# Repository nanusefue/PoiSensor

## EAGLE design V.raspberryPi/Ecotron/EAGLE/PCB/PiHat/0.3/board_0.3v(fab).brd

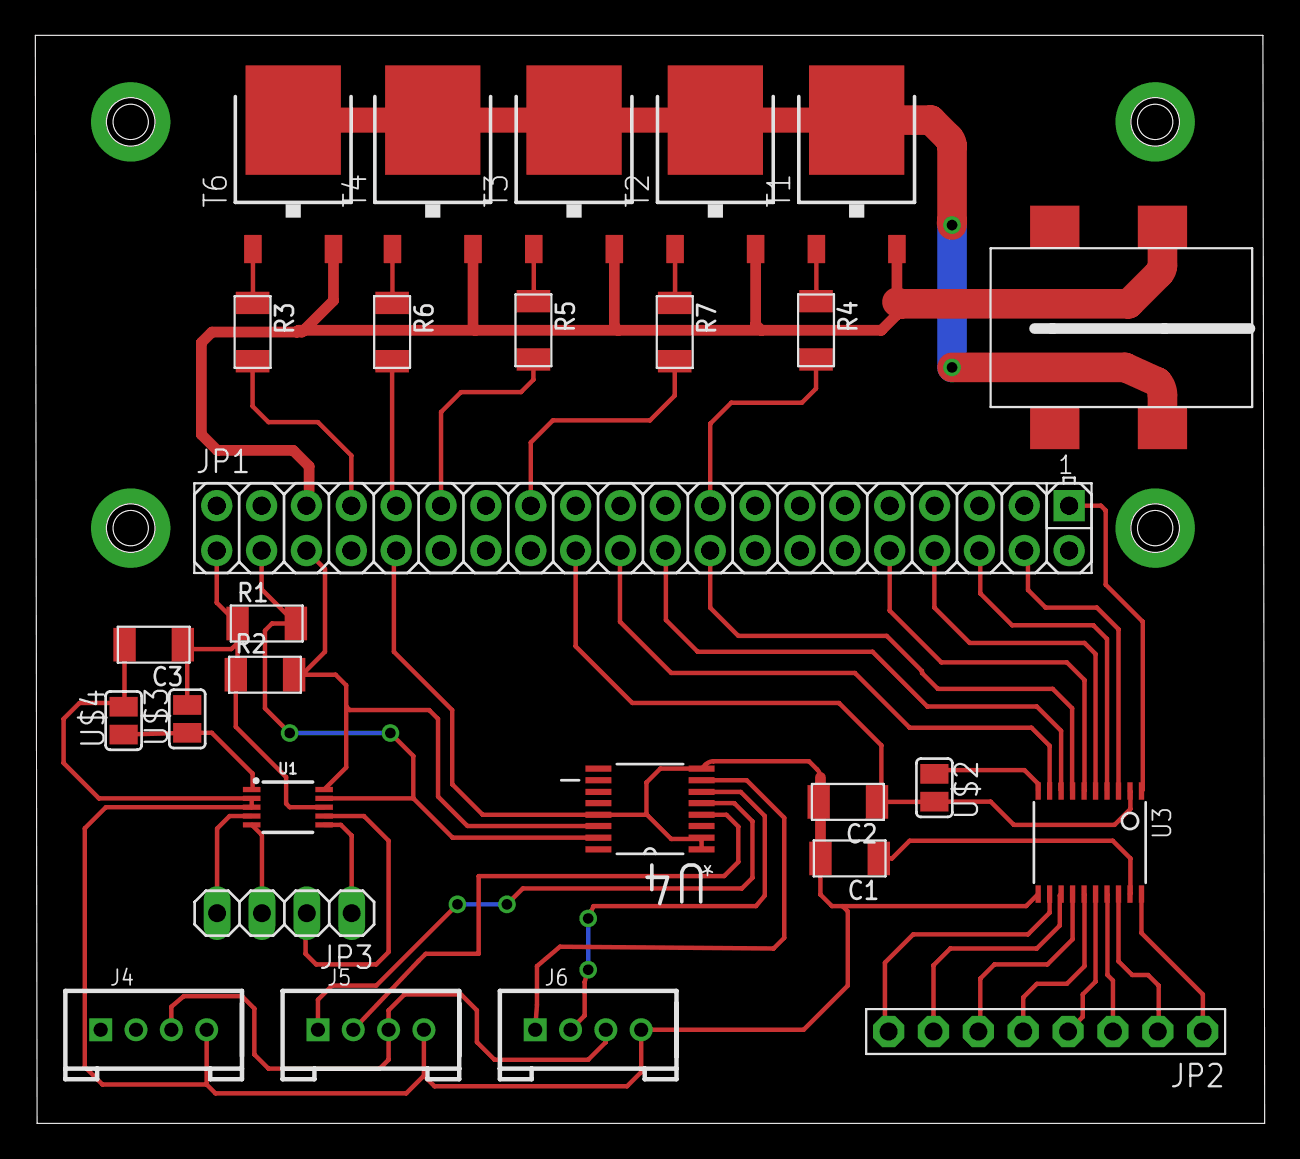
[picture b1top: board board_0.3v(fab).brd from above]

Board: 2 copper layers, 69.6 x 61.6 mm, 29 parts (0 on the bottom side), 44 nets.

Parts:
C1, C2, C3: CAP-US1206FAB; C1206FAB
J1: JACK2.1MM; JACK_2.1MM
J4, J5, J6: 4P-2.0; HW4-2.0
JP1: 2X20
JP2: 1X08-BIG
JP3: 1X04
R1, R2, R3, R4, R5, R6, R7: R1206FAB
T1, T2, T3, T4, T6: TO252
U1: ADS1015; MSOP10
U3: TSSOP20
U4: PCA9546APW,112; SOP65P640X110-16N
U$1: RPI-ZERO; RASPBERRYPI_BASTELSTUBE_V13_RASPI_BOARD_B+_FULL
U$2, U$3, U$4: SOLDER_JUMPER; SJFAB

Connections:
3,3V: C3.1, JP1.1, R1.1, R2.1, U1.8, U$3.2
3,3V_1: C2.1, JP1.17, U3.2, U$2.2
12V: J1.PIN, T1.3, T2.3, T3.3, T4.3, T6.3
A0+: JP3.4, U1.4
A0-: JP3.3, U1.5
A1+: JP3.1, U1.6
A1-: JP3.2, U1.7
ADDR_AD: U1.1, U$3.1, U$4.1
GND: C1.2, C2.2, C3.2, J1.CONTACT, J4.4, J5.4, J6.4, JP1.6, JP1.9, T1.2, T2.2, T3.2, T4.2, T6.2, U1.2, U1.3, U3.11, U4.1, U4.2, U4.8, U4.13, U$4.2
GPIO6: JP1.31, U3.6
GPIO8: JP1.24, R4.2
GPIO9: JP1.21, U3.8
GPIO10: JP1.19, U3.9
GPIO11: JP1.23, U3.7
GPIO13: JP1.33, U3.5
GPIO14: JP1.8, R3.2
GPIO15: JP1.10, R6.2
GPIO18: JP1.12, R5.2
GPIO19: JP1.35, U3.4
GPIO21: JP1.40, U3.1
GPIO23: JP1.16, R7.2
GPIO26: JP1.37, U3.3
unnamed: R3.1, T6.1
unnamed: R4.1, T1.1
unnamed: R6.1, T4.1
unnamed: R7.1, T2.1
unnamed: R5.1, T3.1
unnamed: JP2.8, U3.12
unnamed: JP2.7, U3.13
unnamed: JP2.6, U3.14
unnamed: JP2.5, U3.15
unnamed: JP2.4, U3.16
unnamed: JP2.3, U3.17
unnamed: JP2.2, U3.18
unnamed: JP2.1, U3.20
unnamed: C1.1, U3.19
OE: U3.10, U$2.1
SC0: J5.1, U4.5
SC1: J6.1, U4.7
SCL: JP1.5, R2.2, U1.10, U4.14
SD0: J5.2, U4.4
SD1: J6.2, U4.6
SDA: JP1.3, R1.2, U1.9, U4.15
VCC: J4.3, J5.3, J6.3

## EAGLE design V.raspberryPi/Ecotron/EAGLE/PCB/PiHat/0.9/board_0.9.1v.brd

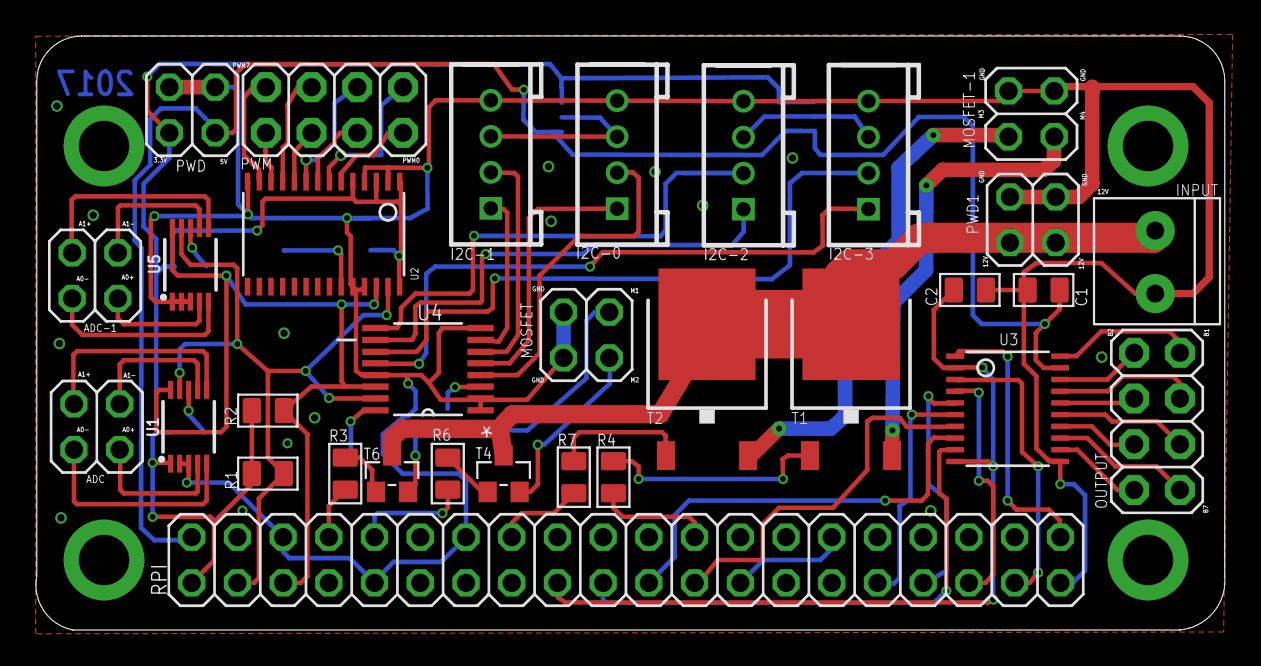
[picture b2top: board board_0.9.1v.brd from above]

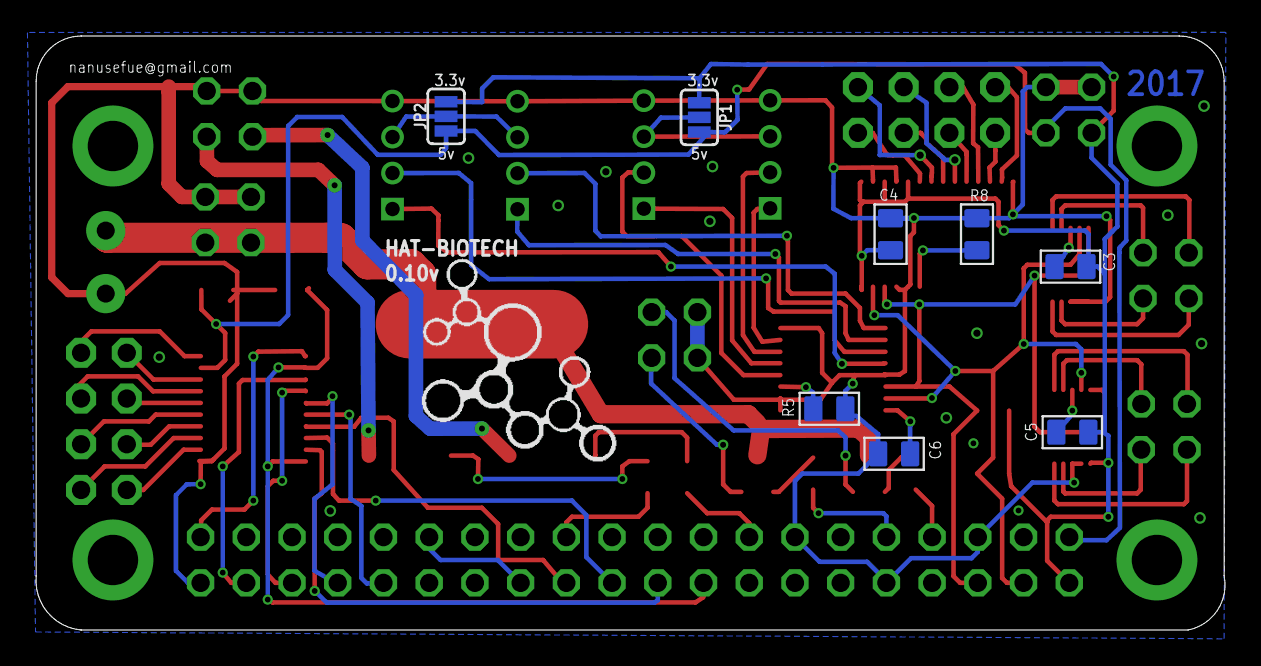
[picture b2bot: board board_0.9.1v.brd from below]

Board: 2 copper layers, 66.1 x 33.0 mm, 39 parts (8 on the bottom side), 66 nets.

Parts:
ADC: 2X02
ADC-1: 2X02
C1, C2: 1uf; C0805
C3, C5: 100nf; C0805
C4, C6: 10uf; C0805
I2C-0, I2C-1, I2C-2, I2C-3: 4P-2.0; HW4-2.0
INPUT: 1X2-3.5MM
JP1, JP2: JUMPER-SMT_3_NO_SILK; SMT-JUMPER_3_NO_SILK
MOSFET: MOSFET; 2X02
MOSFET-1: 2X02
OUTPUT: PINSOUT; 2X04
PWD, PWD1: 2X02
PWM: PWM; 2X04
R1, R2, R3, R4, R5, R6, R7, R8: 10K; R0805
RPI: GPIO; 2X20
T1: T1; TO252
T2: T2; TO252
T4, T6: MOSFET-N; SOT-23
U1, U5: ADS1015; MSOP10
U2: PCA9685; TSSOP28
U3: TXB0108; TSSOP20
U4: PCA9546APW,112; SOP65P640X110-16N

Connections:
3,3V: C3.2, C4.1, C5.2, JP1.1, JP2.3, PWD.1, R1.1, R2.1, RPI.1, U1.1, U2.1, U2.3, U2.5, U2.28
3,3V_1: C2.1, RPI.17, U3.2, U3.10
3,3_1V: C6.1, U4.16
5V: C1.1, JP1.3, JP2.1, PWD.3, RPI.2, U3.19
12V: INPUT.1, PWD1.1, PWD1.3, T1.3, T2.3, T4.3, T6.3
A0+: ADC.3, U1.4
A0+_1: ADC-1.3, U5.4
A0-: ADC.1, U1.5
A0-_1: ADC-1.1, U5.5
A1+: ADC.2, U1.6
A1+_1: ADC-1.2, U5.6
A1-: ADC.4, U1.7
A1-_1: ADC-1.4, U5.7
B1: OUTPUT.7, U3.20
B2: OUTPUT.8, U3.18
B3: OUTPUT.5, U3.17
B4: OUTPUT.6, U3.16
B5: OUTPUT.3, U3.15
B6: OUTPUT.4, U3.14
B7: OUTPUT.1, U3.13
B8: OUTPUT.2, U3.12
GND: C1.2, C2.2, C4.2, C6.2, I2C-0.4, I2C-1.4, I2C-2.4, I2C-3.4, INPUT.2, MOSFET.3, MOSFET.4, MOSFET-1.3, MOSFET-1.4, PWD.2, PWD.4, PWD1.2, PWD1.4, R5.2, R8.1, RPI.6, RPI.9, RPI.14, RPI.25, RPI.30, RPI.39, U1.2, U1.3, U2.2, U2.4, U2.14, U2.24, U2.25, U3.11, U4.1, U4.2, U4.8, U4.13, U5.1, U5.2, U5.3
GPIO6: RPI.31, U3.6
GPIO8: R4.2, RPI.24
GPIO9: RPI.21, U3.8
GPIO10: RPI.19, U3.9
GPIO11: RPI.23, U3.7
GPIO13: RPI.33, U3.5
GPIO14: R3.2, RPI.8
GPIO15: R6.2, RPI.10
GPIO19: RPI.35, U3.4
GPIO21: RPI.40, U3.1
GPIO23: R7.2, RPI.16
GPIO26: RPI.37, U3.3
MOSFET_1: MOSFET.1, T6.2
MOSFET_2: MOSFET.2, T4.2
MOSFET_3: MOSFET-1.2, T2.2
MOSFET_4: MOSFET-1.1, T1.2
unnamed: R3.1, T6.1
unnamed: R5.1, U4.3
unnamed: C3.1, U5.8
unnamed: R4.1, T1.1
unnamed: R6.1, T4.1
unnamed: R7.1, T2.1
unnamed: C5.1, U1.8
unnamed: R8.2, U2.23
PWM0: PWM.2, U2.6
PWM1: PWM.1, U2.7
PWM2: PWM.4, U2.8
PWM3: PWM.3, U2.9
PWM4: PWM.6, U2.10
PWM5: PWM.5, U2.11
PWM6: PWM.8, U2.12
PWM7: PWM.7, U2.13
SC0: I2C-0.1, U4.5
SC1: I2C-1.1, U4.7
SC2: I2C-2.1, U4.10
SC3: I2C-3.1, U4.12
SCL: R2.2, RPI.5, U1.10, U2.26, U4.14, U5.10
SD0: I2C-0.2, U4.4
SD1: I2C-1.2, U4.6
SD2: I2C-2.2, U4.9
SD3: I2C-3.2, U4.11
SDA: R1.2, RPI.3, U1.9, U2.27, U4.15, U5.9
VCC_I2C_1: I2C-0.3, I2C-1.3, JP1.2
VCC_I2C_2: I2C-2.3, I2C-3.3, JP2.2

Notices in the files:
parts and their libraries:
SparkFun-IC-Conversion: Licensing: Creative Commons ShareAlike 4.0 International - https://creativecommons.org/licenses/by-sa/4.0
